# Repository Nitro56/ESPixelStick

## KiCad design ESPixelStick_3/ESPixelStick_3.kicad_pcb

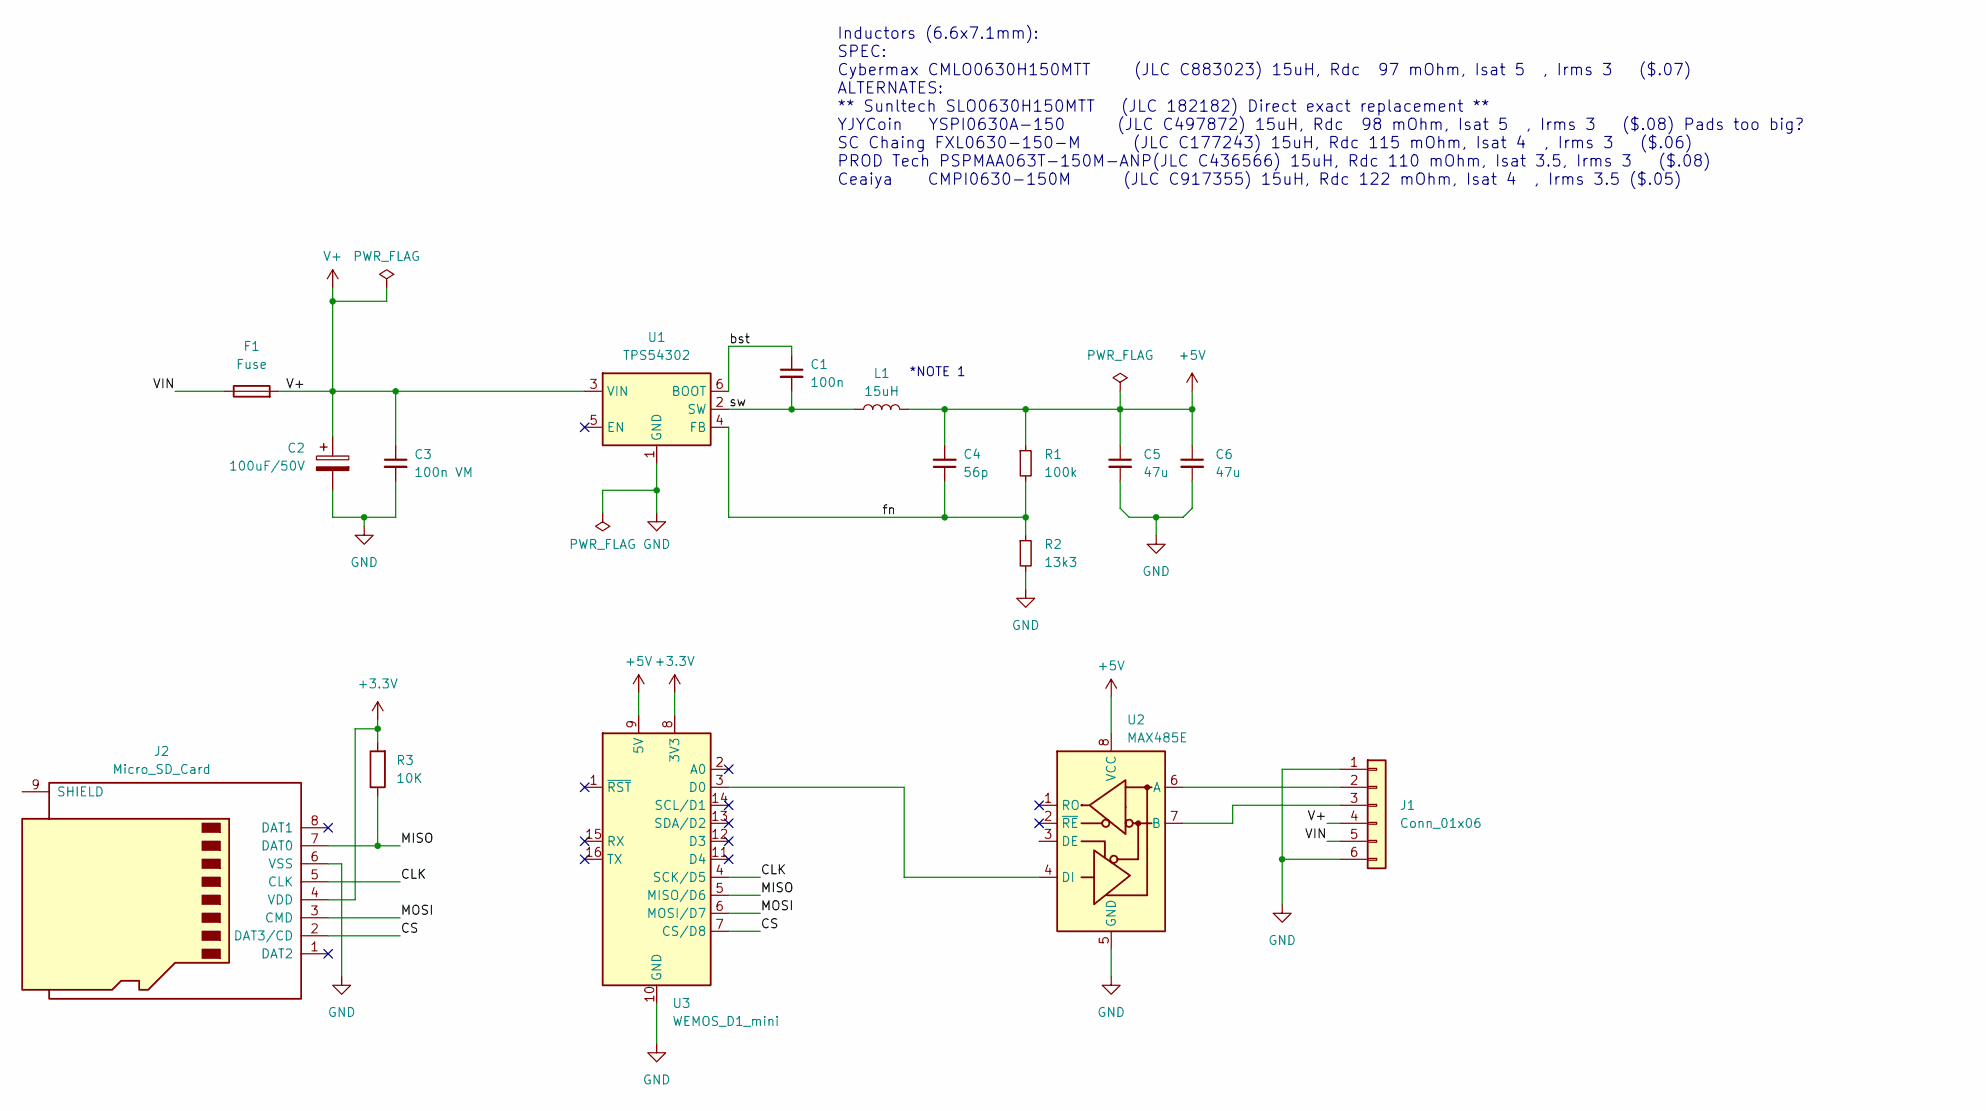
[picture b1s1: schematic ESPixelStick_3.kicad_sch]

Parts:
C1: 100n; C_0603_1608Metric; LCSC Part # C1525
C2: 100uF/50V; CP_Elec_6.3x7.7
C3: 100n VM; C_0603_1608Metric; LCSC Part # C307331
C4: 56p; C_0603_1608Metric; LCSC Part # C107007
C5, C6: 47u; C_0805_2012Metric; LCSC Part # C16780
F1: Fuse; Fuse_Blade_Mini_directSolder
J1: Conn_01x06; PhoenixContact_MC_1,5_6-G-3.81_1x06_P3.81mm_Horizontal
J2: Micro_SD_Card; microSD_HC_Wuerth_693072010801
L1: 15uH; L_Taiyo-Yuden_MD-3030; LCSC Part # C883023
R1: 100k; R_0603_1608Metric; LCSC Part # C60491
R2: 13k3; R_0603_1608Metric; LCSC Part # C274352
R3: 10K; R_0603_1608Metric
U1: TPS54302; SOT-23-6
U2: MAX485E; SOIC-8_3.9x4.9mm_P1.27mm
U3: WEMOS_D1_mini; WEMOS_D1_mini_light

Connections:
+3.3V: J2.4 (VDD), R3.2, U3.8 (3V3)
+5V: C4.2, C5.1, C6.1, L1.2, R1.1, U2.8 (VCC), U3.9 (5V)
/CLK: J2.5 (CLK), U3.4 (SCK/D5)
/CS: J2.2 (DAT3/CD), U3.7 (CS/D8)
/MISO: J2.7 (DAT0), R3.1, U3.5 (MISO/D6)
/MOSI: J2.3 (CMD), U3.6 (MOSI/D7)
/VIN: F1.1, J1.5
/bst: C1.1, U1.6 (BOOT)
/fn: C4.1, R1.2, R2.1, U1.4 (FB)
/sw: C1.2, L1.1, U1.2 (SW)
GND: C2.2, C3.2, C5.2, C6.2, J1.1, J1.6, J2.6 (VSS), R2.2, U1.1 (GND), U2.5 (GND), U3.10 (GND)
unnamed: J1.2, U2.6 (A)
unnamed: J1.3, U2.7 (B)
unnamed: U2.4 (DI), U3.3 (D0)
V+: C2.1, C3.1, F1.2, J1.4, U1.3 (VIN)

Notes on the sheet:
Inductors (6.6x7.1mm): SPEC: Cybermax CMLO0630H150MTT (JLC C883023) 15uH, Rdc 97 mOhm, Isat 5 , Irms 3 ($.07) ALTERNATES: ** Sunltech SLO0630H150MTT (JLC 182182) Direct exact replacement ** YJYCoin YSPI0630A-150 (JLC C497872) 15uH, Rdc 98 mOhm, Isat 5 , Irms 3 ($.08) Pads too big? SC Chaing FXL0630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
*NOTE 1

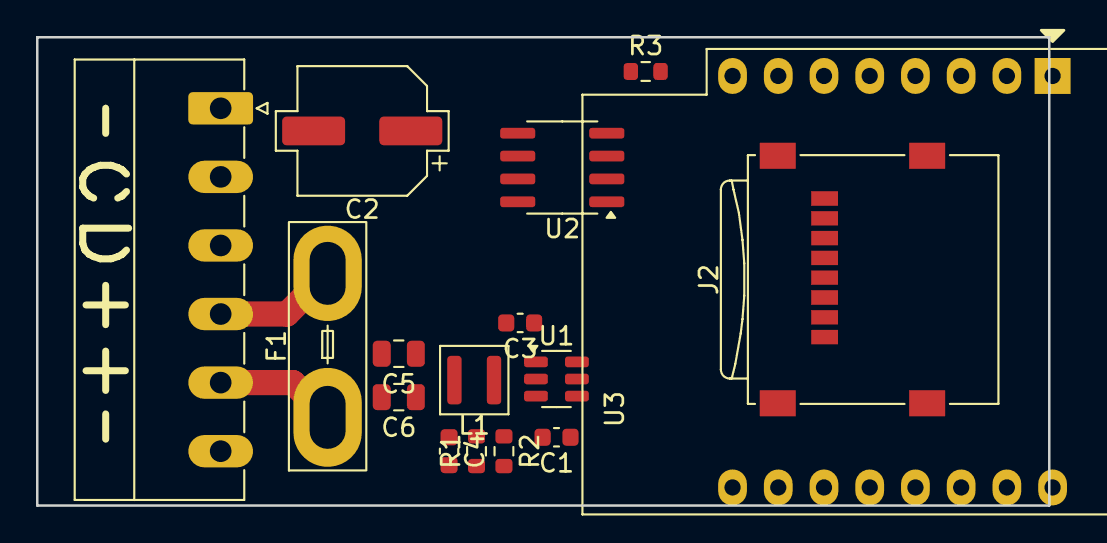
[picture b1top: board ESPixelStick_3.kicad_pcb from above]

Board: 2 copper layers, 56.2 x 26.0 mm, 16 parts (0 on the bottom side), 15 nets.

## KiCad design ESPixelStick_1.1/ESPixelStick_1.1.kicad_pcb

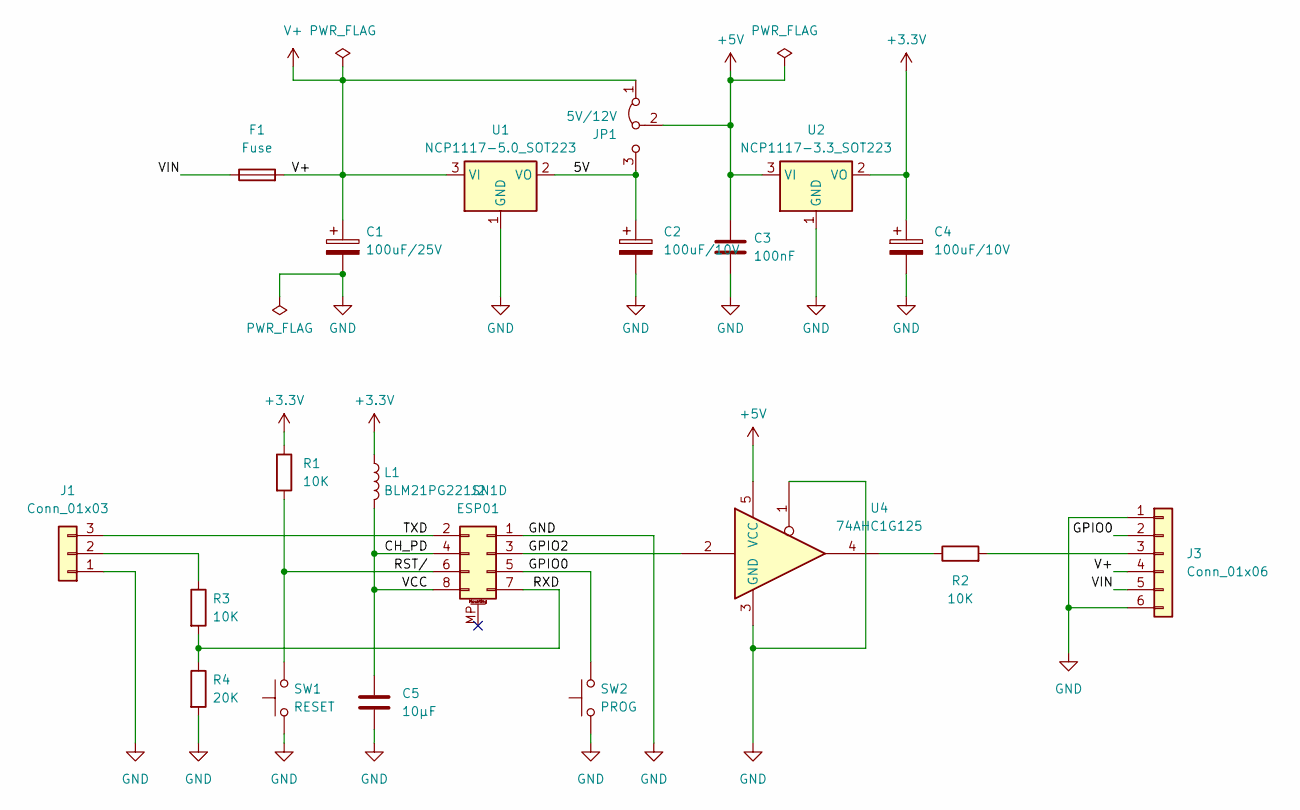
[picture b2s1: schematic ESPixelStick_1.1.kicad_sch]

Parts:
C1: 100uF/25V; CP_Radial_D8.0mm_P3.50mm
C2, C4: 100uF/10V; CP_Radial_D5.0mm_P2.00mm
C3: 100nF; C_0603_1608Metric
C5: 10µF; C_0603_1608Metric
F1: Fuse; Fuse_Blade_Mini_directSolder
J1: Conn_01x03; PinHeader_1x03_P2.54mm_Vertical
J2: ESP01; PinSocket_2x04_P2.54mm_Vertical
J3: Conn_01x06; PhoenixContact_MC_1,5_6-G-3.81_1x06_P3.81mm_Horizontal
JP1: 5V/12V; PinHeader_1x03_P2.54mm_Vertical
L1: BLM21PG221SN1D; L_0603_1608Metric
R1, R2, R3: 10K; R_0603_1608Metric
R4: 20K; R_0603_1608Metric
SW1: RESET; SW_PUSH_6mm
SW2: PROG; SW_PUSH_6mm
U1: NCP1117-5.0_SOT223; SOT-223-3_TabPin2
U2: NCP1117-3.3_SOT223; SOT-223-3_TabPin2
U4: 74AHC1G125; SC-74A-5_1.55x2.9mm_P0.95mm

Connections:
+3.3V: C4.1, L1.1, R1.1, U2.2 (VO)
+5V: C3.1, JP1.2 (C), U2.3 (VI), U4.5 (VCC)
/5V: C2.1, JP1.3 (B), U1.2 (VO)
/CH_PD: C5.1, J2.4, J2.8, L1.2
/GPIO0: J2.5, J3.2, SW2.2
/GPIO2: J2.3, U4.2
/RST/: J2.6, R1.2, SW1.2
/RXD: J2.7, R3.2, R4.1
/TXD: J1.3, J2.2
/VIN: F1.1, J3.5
GND: C1.2, C2.2, C3.2, C4.2, C5.2, J1.1, J2.1, J3.1, J3.6, R4.2, SW1.1, SW2.1, U1.1 (GND), U2.1 (GND), U4.1, U4.3 (GND)
unnamed: J1.2, R3.1
unnamed: J3.3, R2.2
unnamed: R2.1, U4.4
V+: C1.1, F1.2, J3.4, JP1.1 (A), U1.3 (VI)

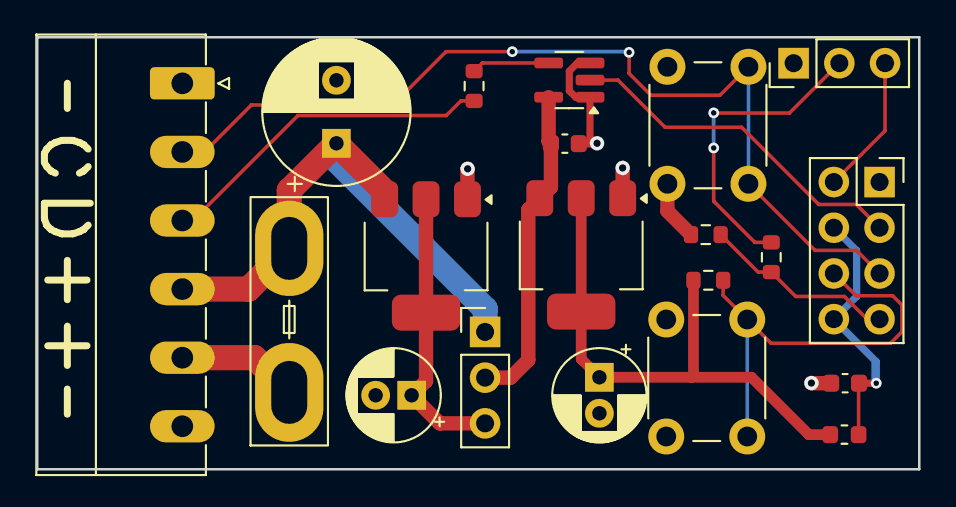
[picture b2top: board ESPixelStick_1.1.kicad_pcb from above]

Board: 2 copper layers, 49.0 x 24.0 mm, 20 parts (0 on the bottom side), 15 nets.
